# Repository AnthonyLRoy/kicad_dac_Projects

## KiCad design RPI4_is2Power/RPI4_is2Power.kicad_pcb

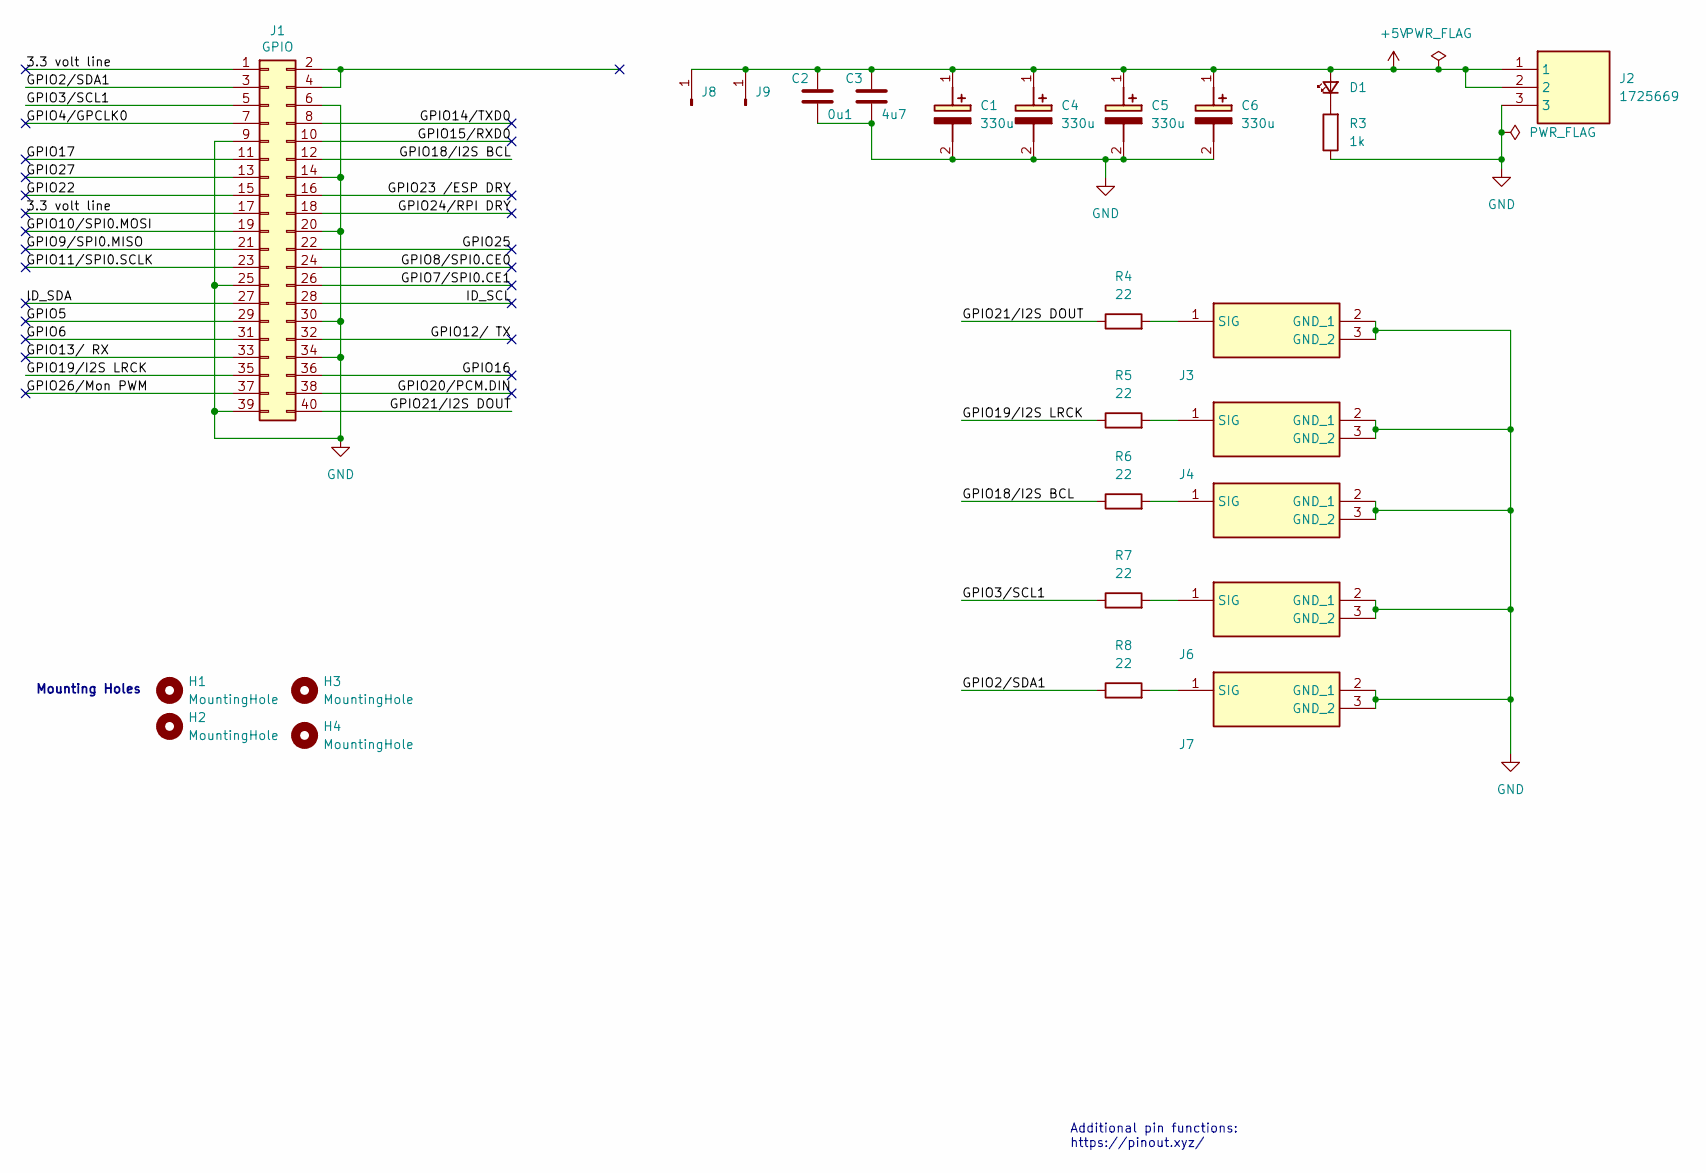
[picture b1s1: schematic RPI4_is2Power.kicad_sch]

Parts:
C1, C4, C5, C6: 330u; CAPPRD350W60D800H1300; Mouser Part Number 647-RNU1C331MDN1KX
C2: 0u1; C_0603_1608Metric_Pad1.08x0.95mm_HandSolder
C3: 4u7; CP_Radial_D5.0mm_P2.00mm
D1: LS_R976; LEDC2012X40N; Mouser Part Number 720-LSR976D5178
H1, H2, H3, H4: MountingHole; MountingHole_2.5mm
J1: GPIO; PinSocket_2x20_P2.54mm_Vertical
J2: 1725669; Mouser Part Number 651-1725669
J3, J4, J5, J6, J7: U.FL-R-SMT-1_80_; UFLRSMT180; Manufacturer_Part_Number U.FL-R-SMT-1(80)
J8, J9: Conn_01x01_Pin; Pin_D1.2mm_L11.3mm_W3.0mm_Flat
R3: 1k; R_0402_1005Metric
R4, R5, R6, R7, R8: 22; R_0402_1005Metric

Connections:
+5V: C1.1 (+), C2.1, C3.1, C4.1 (+), C5.1 (+), C6.1 (+), D1.2 (A), J2.1, J2.2, J8.1 (Pin_1_1), J9.1 (Pin_1_1)
/3.3 volt line: J1.1, J1.17
/GPIO2/SDA1: J1.3, R8.1
/GPIO3/SCL1: J1.5, R7.1
/GPIO4/GPCLK0: J1.7
/GPIO5: J1.29
/GPIO6: J1.31
/GPIO7/SPI0.CE1: J1.26
/GPIO8/SPI0.CE0: J1.24
/GPIO9/SPI0.MISO: J1.21
/GPIO10/SPI0.MOSI: J1.19
/GPIO11/SPI0.SCLK: J1.23
/GPIO12/ TX: J1.32
/GPIO13/ RX: J1.33
/GPIO14/TXD0: J1.8
/GPIO15/RXD0: J1.10
/GPIO16: J1.36
/GPIO17: J1.11
/GPIO18/I2S BCL: J1.12, R6.1
/GPIO19/I2S LRCK: J1.35, R5.1
/GPIO20/PCM.DIN: J1.38
/GPIO21/I2S DOUT: J1.40, R4.1
/GPIO22: J1.15
/GPIO23 /ESP DRY: J1.16
/GPIO24/RPI DRY: J1.18
/GPIO25: J1.22
/GPIO26/Mon PWM: J1.37
/GPIO27: J1.13
/ID_SCL: J1.28
/ID_SDA: J1.27
GND: C1.2 (-), C2.2, C3.2, C4.2 (-), C5.2 (-), C6.2 (-), J1.6, J1.9, J1.14, J1.20, J1.25, J1.30, J1.34, J1.39, J2.3, J3.2 (GND_1), J3.3 (GND_2), J4.2 (GND_1), J4.3 (GND_2), J5.2 (GND_1), J5.3 (GND_2), J6.2 (GND_1), J6.3 (GND_2), J7.2 (GND_1), J7.3 (GND_2), R3.1
unnamed: D1.1 (K), R3.2
unnamed: J3.1 (SIG), R4.2
unnamed: J4.1 (SIG), R5.2
unnamed: J5.1 (SIG), R6.2
unnamed: J6.1 (SIG), R7.2
unnamed: J7.1 (SIG), R8.2

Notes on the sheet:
Mounting Holes
Additional pin functions: https://pinout.xyz/

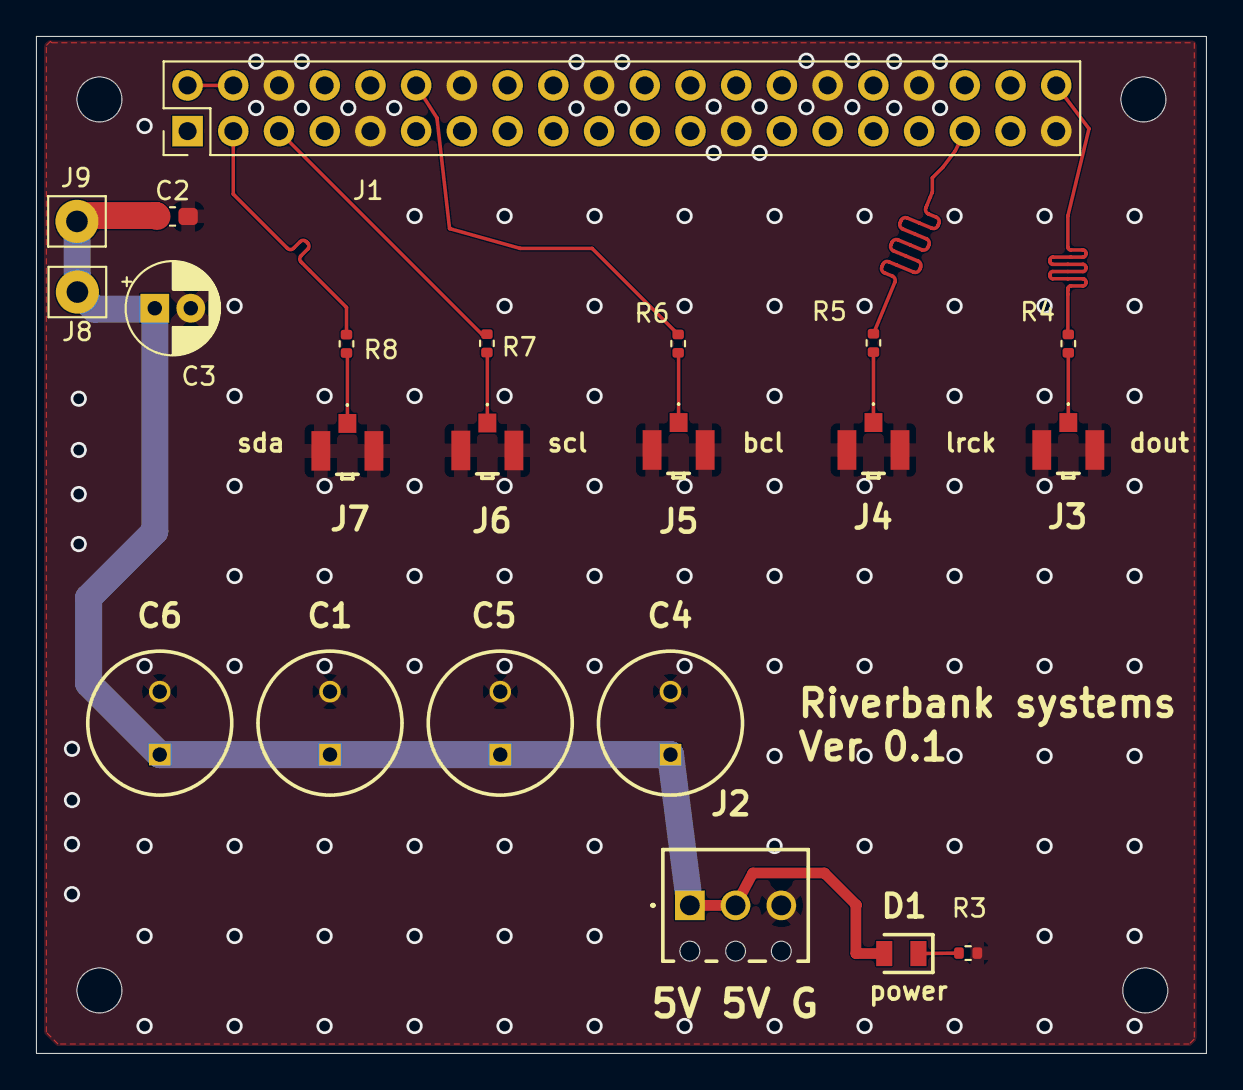
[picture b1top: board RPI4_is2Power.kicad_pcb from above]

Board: 2 copper layers, 65.0 x 56.5 mm, 26 parts (0 on the bottom side), 14 nets.

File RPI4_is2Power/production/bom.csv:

Designator,Footprint,Quantity,Value,LCSC Part #
"C1, C4, C5, C6",CAPPRD350W60D800H1300,4,330u,
C2,0603,1,0u1,
C3,CP_Radial_D5.0mm_P2.00mm,1,4u7,
D1,LEDC2012X40N,1,LS_R976,
"H1, H2, H3, H4",MountingHole_2.5mm,4,MountingHole,
J1,PinSocket_2x20_P2.54mm_Vertical,1,GPIO,
J2,1725669,1,1725669,
"J3, J4, J5, J6, J7",UFLRSMT180,5,U.FL-R-SMT-1_80_,
"J8, J9",Pin_D1.2mm_L11.3mm_W3.0mm_Flat,2,Conn_01x01_Pin,
R3,0402,1,1k,
"R4, R5, R6, R7, R8",0402,5,22,

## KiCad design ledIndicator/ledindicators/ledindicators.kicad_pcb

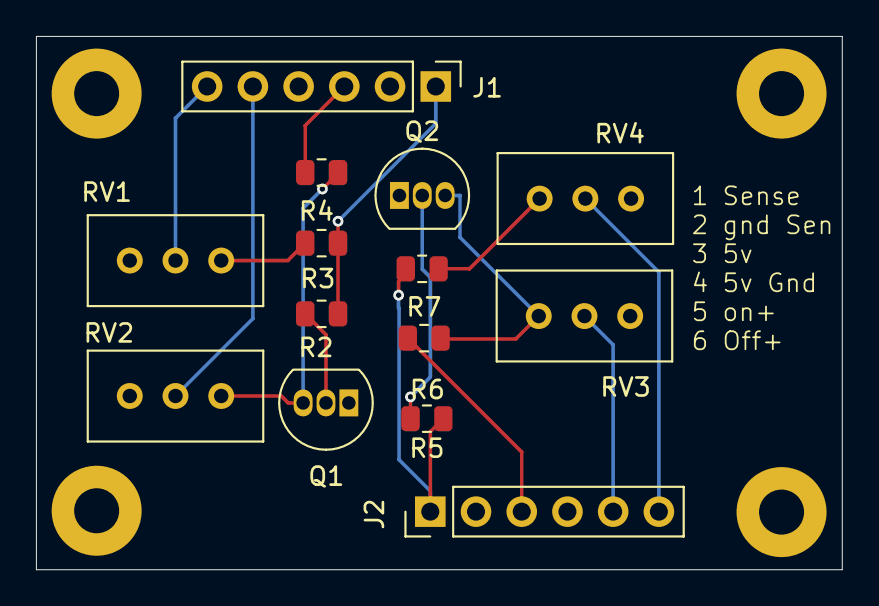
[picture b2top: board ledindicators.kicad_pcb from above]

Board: 2 copper layers, 44.8 x 29.6 mm, 18 parts (0 on the bottom side), 15 nets.

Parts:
H1, H2, H3, H4: MountingHole; MountingHole_2.5mm_Pad
J1, J2: Conn_01x06_Pin; PinHeader_1x06_P2.54mm_Vertical
Q1, Q2: 2N3904; TO-92_Inline
R2, R5: 10k; R_0805_2012Metric
R3, R4, R6, R7: 330R; R_0805_2012Metric
RV1, RV2, RV3, RV4: 100; Potentiometer_Bourns_3296W_Vertical

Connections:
GND: J1.2, J1.4, J2.2, J2.4, Q1.1 (E), Q2.1 (E)
unnamed: J1.1, R2.1, R3.2
unnamed: J1.3, R4.2
unnamed: J1.5, RV2.2
unnamed: J1.6, RV1.2
unnamed: J2.1, R5.1, R7.2
unnamed: J2.3, R6.2
unnamed: J2.5, RV3.2
unnamed: J2.6, RV4.2
unnamed: Q1.2 (B), R2.2
unnamed: Q1.3 (C), R4.1, RV2.1
unnamed: Q2.2 (B), R5.2
unnamed: Q2.3 (C), R6.1, RV3.1
unnamed: R3.1, RV1.1
unnamed: R7.1, RV4.1

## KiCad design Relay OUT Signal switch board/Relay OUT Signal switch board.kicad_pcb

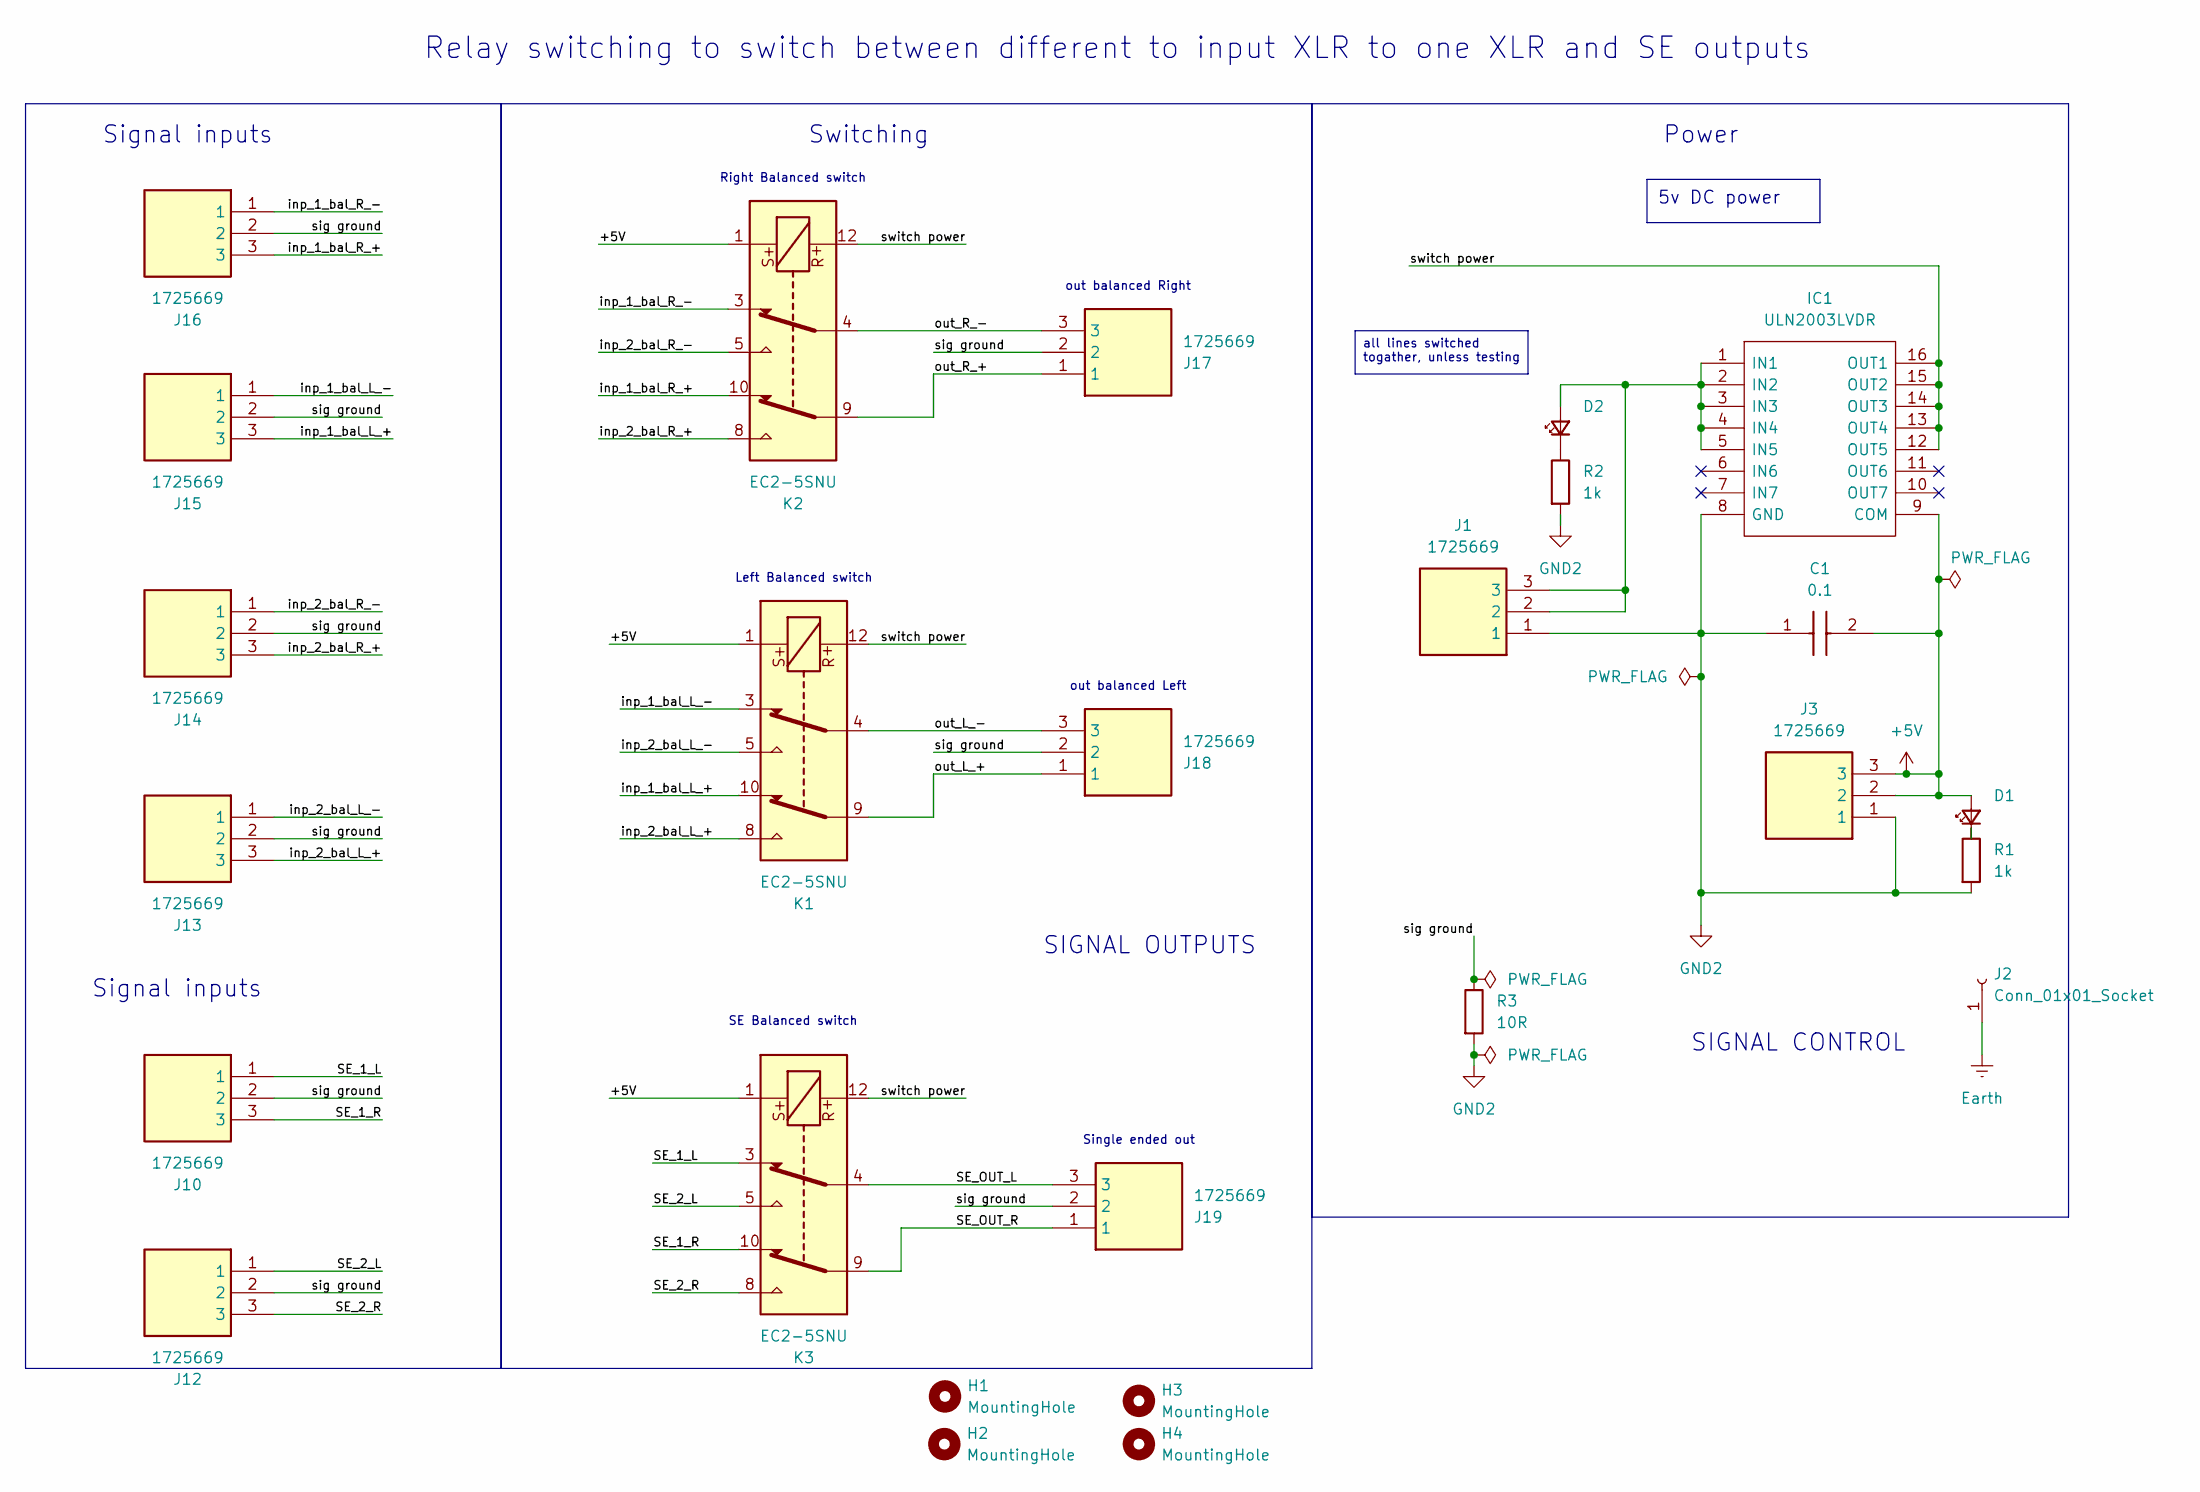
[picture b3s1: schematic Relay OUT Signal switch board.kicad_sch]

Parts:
C1: 0.1; C_0603_1608Metric; Mouser Part Number 80-C0603C104K4R3190
D1, D2: LS_R976; LEDC2012X40N; Mouser Part Number 720-LSR976D5178
H1, H2, H3, H4: MountingHole; MountingHole_2.5mm
IC1: ULN2003LVDR; SOIC127P780X200-16N; Manufacturer_Part_Number ULN2003LVDR; Mouser Part Number 595-ULN2003LVDR
J1, J3, J10, J12, J13, J14, J15, J16, J17, J18, J19: 1725669; Mouser Part Number 651-1725669
J2: Conn_01x01_Socket; PinHeader_1x01_P1.00mm_Vertical
K1, K2, K3: EC2-5SNU; Relay_DPDT_Kemet_EC2
R1, R2: 1k; R_0603_1608Metric
R3: 10R; R_0603_1608Metric

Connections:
+5V: C1.2, D1.2 (A), IC1.9 (COM), J3.2, J3.3, K1.1, K2.1, K3.1
/SE_1_L: J10.1, K3.3
/SE_1_R: J10.3, K3.10
/SE_2_L: J12.1, K3.5
/SE_2_R: J12.3, K3.8
/SE_OUT_L: J19.3, K3.4
/SE_OUT_R: J19.1, K3.9
/inp_1_bal_L_+: J15.3, K1.10
/inp_1_bal_L_-: J15.1, K1.3
/inp_1_bal_R_+: J16.3, K2.10
/inp_1_bal_R_-: J16.1, K2.3
/inp_2_bal_L_+: J13.3, K1.8
/inp_2_bal_L_-: J13.1, K1.5
/inp_2_bal_R_+: J14.3, K2.8
/inp_2_bal_R_-: J14.1, K2.5
/out_L_+: J18.1, K1.9
/out_L_-: J18.3, K1.4
/out_R_+: J17.1, K2.9
/out_R_-: J17.3, K2.4
/sig ground: J10.2, J12.2, J13.2, J14.2, J15.2, J16.2, J17.2, J18.2, J19.2, R3.1
Earth: J2.1
GND2: C1.1, IC1.8 (GND), J1.1, J3.1, R1.2, R2.2, R3.2
unnamed: D1.1 (K), R1.1
unnamed: D2.1 (K), R2.1

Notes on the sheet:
all lines switched togather, unless testing
5v DC power
out balanced Left
Left Balanced switch
Switching
Power
out balanced Right
Single ended out
Signal inputs
SIGNAL CONTROL
SE Balanced switch
Relay switching to switch between different to input XLR to one XLR and SE outputs
Right Balanced switch
SIGNAL OUTPUTS

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
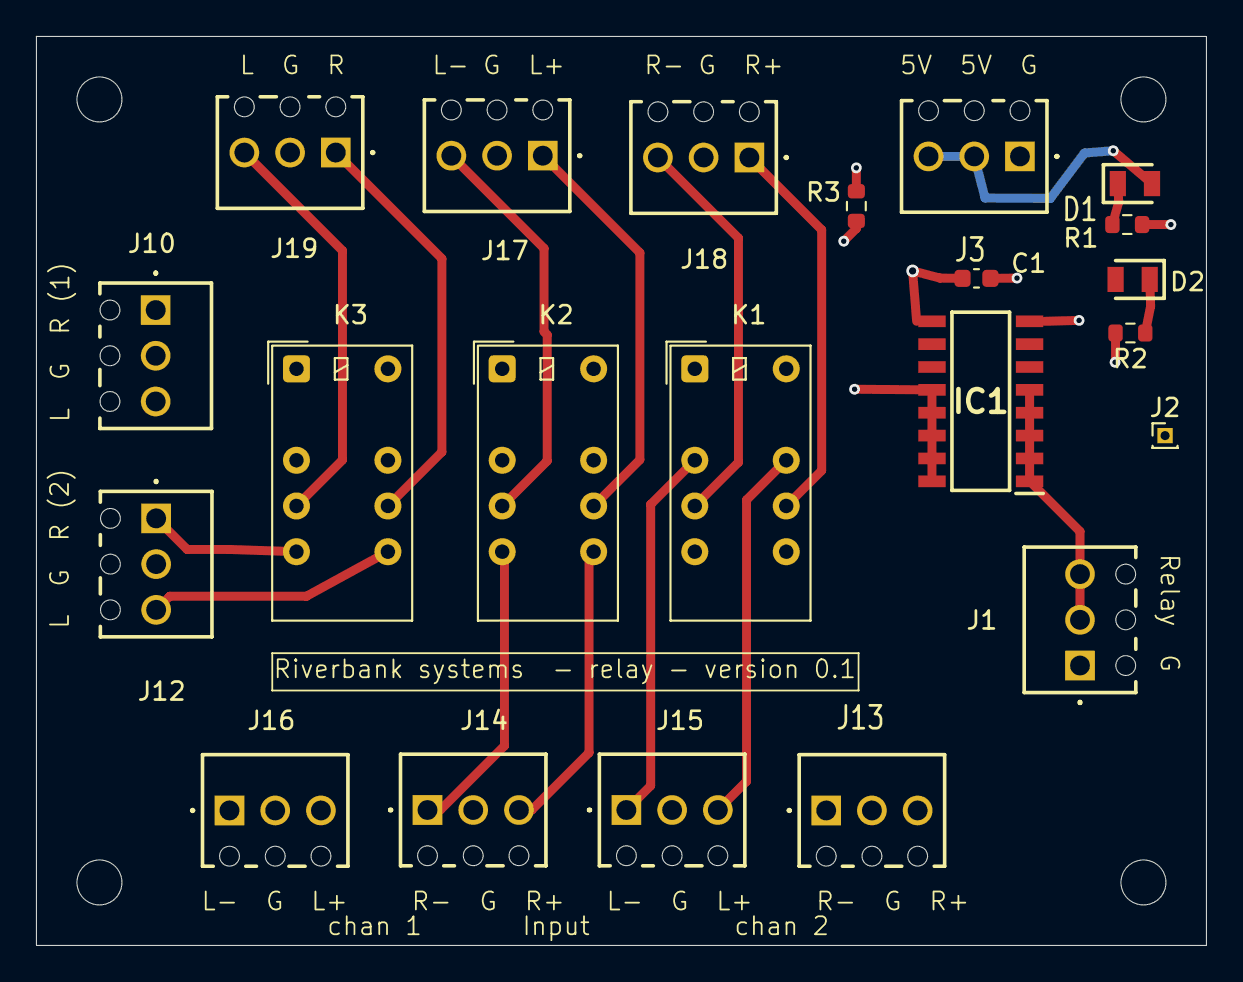
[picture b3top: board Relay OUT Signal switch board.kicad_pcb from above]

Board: 6 copper layers, 65.0 x 50.5 mm, 26 parts (0 on the bottom side), 25 nets.

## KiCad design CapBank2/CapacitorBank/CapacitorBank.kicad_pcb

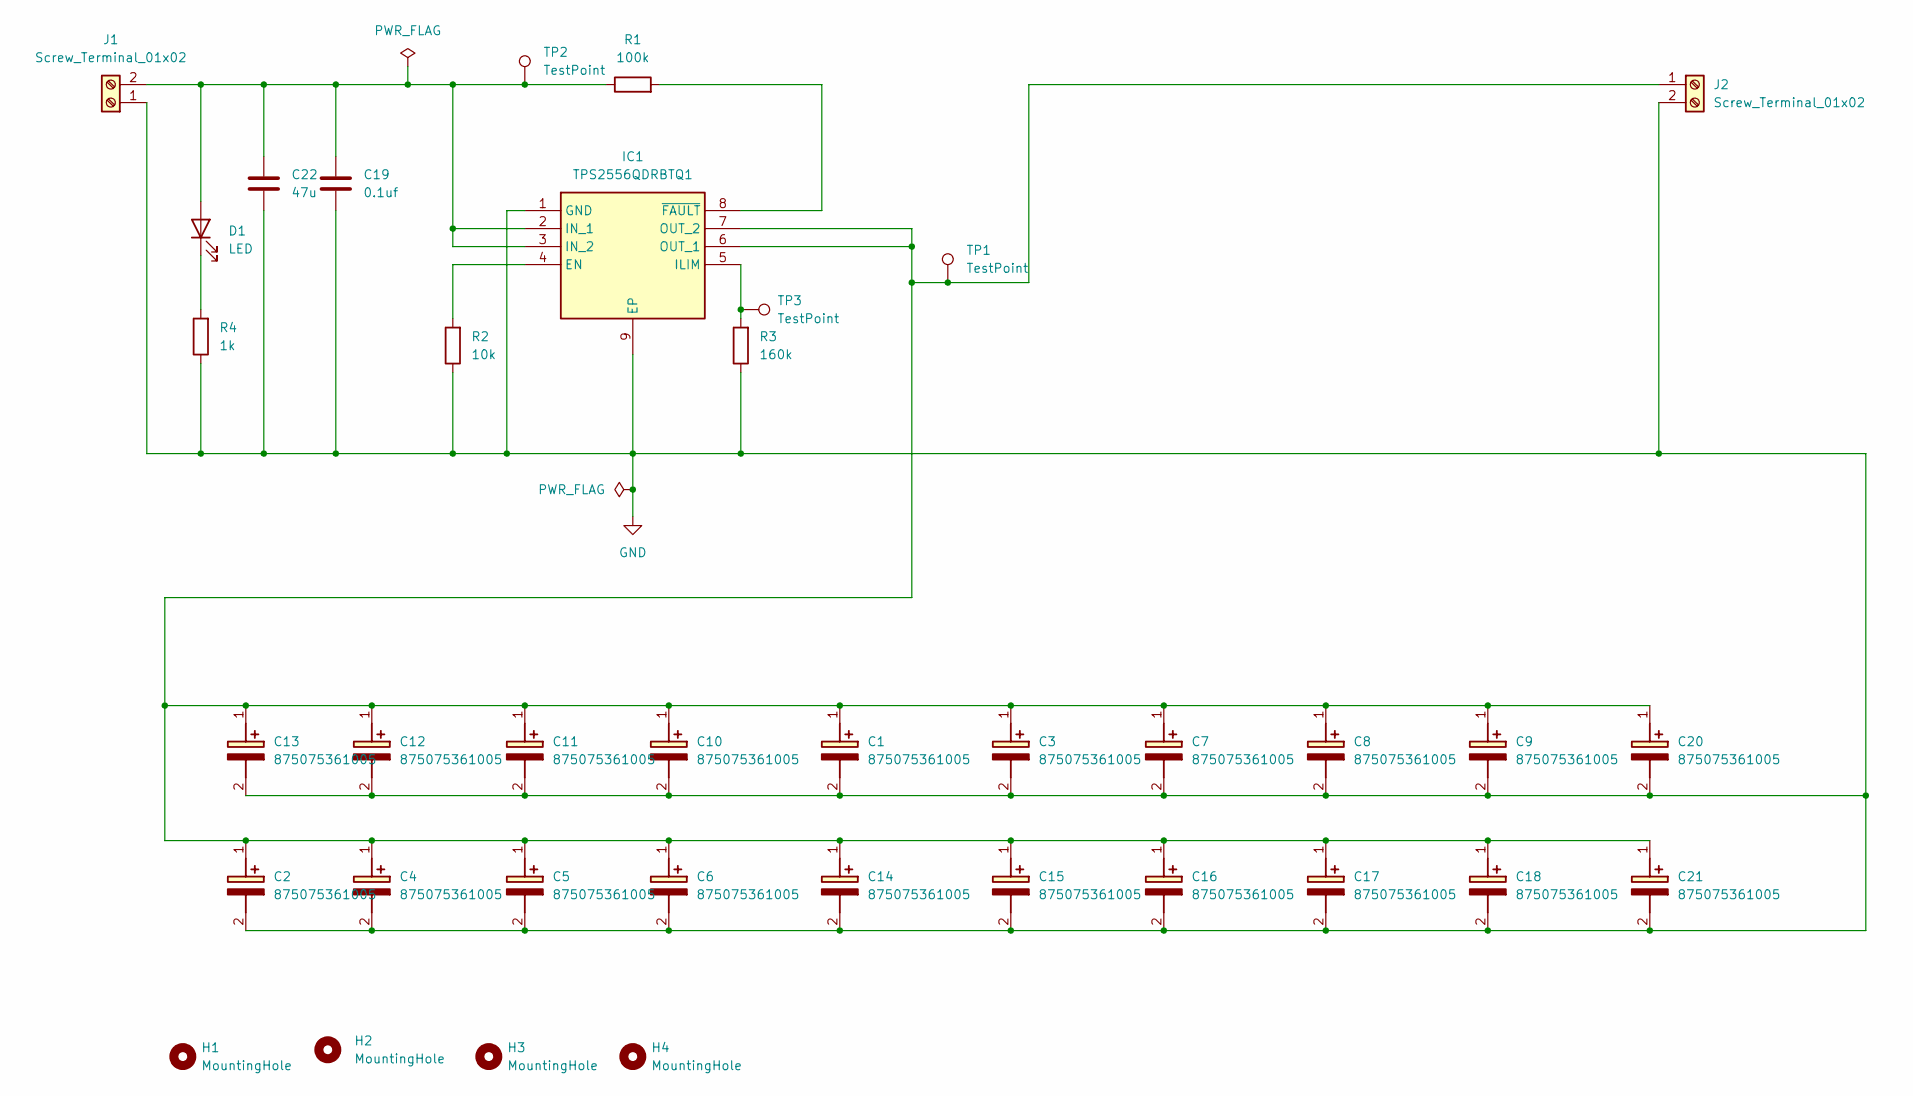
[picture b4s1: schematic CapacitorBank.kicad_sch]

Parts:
C1, C2, C3, C4, C5, C6, C7, C8, C9, C10, C11, C12, C13, C14, C15, C16, C17, C18, C20, C21: 875075361005; CAPAE1030X1270N; Mouser Part Number 710-875075361005
C19: 0.1uf; C_0805_2012Metric
C22: 47u; C_0805_2012Metric
D1: LED; LED_0603_1608Metric_Pad1.05x0.95mm_HandSolder
H1, H2, H3, H4: MountingHole; MountingHole_3.2mm_M3
IC1: TPS2556QDRBTQ1; SON65P300X300X100-9N-D; Mouser Part Number 595-TPS2556QDRBTQ1
J1, J2: Screw_Terminal_01x02; TerminalBlock_483132_2P_P7.62mm
R1: 100k; R_0805_2012Metric_Pad1.20x1.40mm_HandSolder
R2: 10k; R_0805_2012Metric_Pad1.20x1.40mm_HandSolder
R3: 160k; R_0805_2012Metric_Pad1.20x1.40mm_HandSolder
R4: 1k; R_0805_2012Metric_Pad1.20x1.40mm_HandSolder
TP1, TP2, TP3: TestPoint; TestPoint_Pad_1.5x1.5mm

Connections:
GND: C1.2 (-), C2.2 (-), C3.2 (-), C4.2 (-), C5.2 (-), C6.2 (-), C7.2 (-), C8.2 (-), C9.2 (-), C10.2 (-), C11.2 (-), C12.2 (-), C13.2 (-), C14.2 (-), C15.2 (-), C16.2 (-), C17.2 (-), C18.2 (-), C19.2, C20.2 (-), C21.2 (-), C22.2, IC1.1 (GND), IC1.9 (EP), J1.1, J2.2, R2.1, R3.1, R4.1
unnamed: C1.1 (+), C2.1 (+), C3.1 (+), C4.1 (+), C5.1 (+), C6.1 (+), C7.1 (+), C8.1 (+), C9.1 (+), C10.1 (+), C11.1 (+), C12.1 (+), C13.1 (+), C14.1 (+), C15.1 (+), C16.1 (+), C17.1 (+), C18.1 (+), C20.1 (+), C21.1 (+), IC1.6 (OUT_1), IC1.7 (OUT_2), J2.1, TP1.1
unnamed: C19.1, C22.1, D1.2 (A), IC1.2 (IN_1), IC1.3 (IN_2), J1.2, R1.1, TP2.1
unnamed: D1.1 (K), R4.2
unnamed: IC1.4 (EN), R2.2
unnamed: IC1.5 (ILIM), R3.2, TP3.1
unnamed: IC1.8 (~FAULT), R1.2

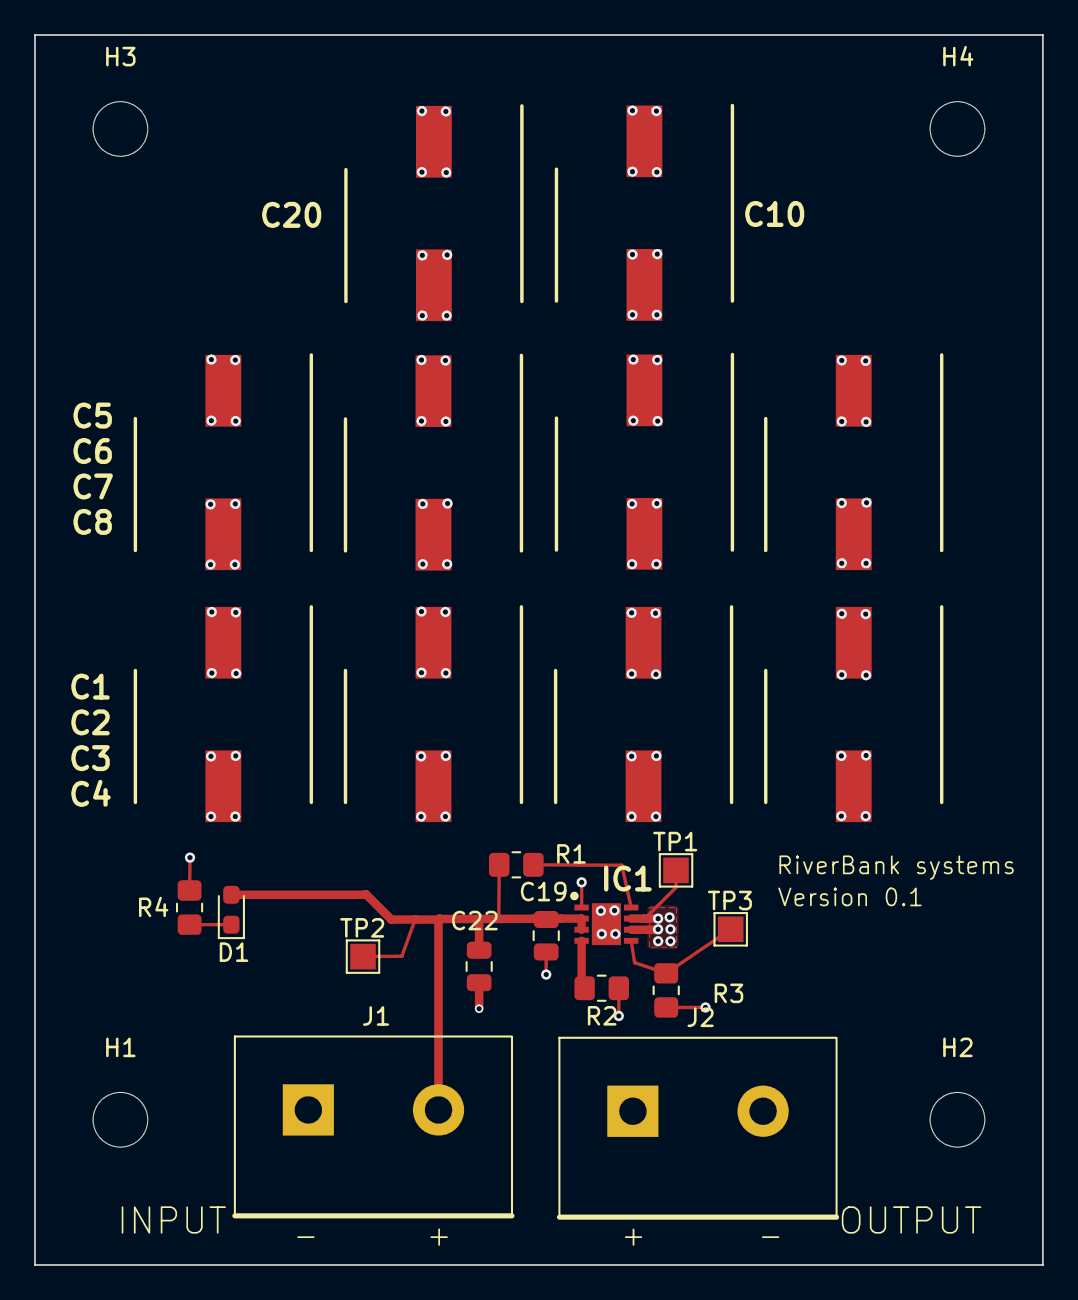
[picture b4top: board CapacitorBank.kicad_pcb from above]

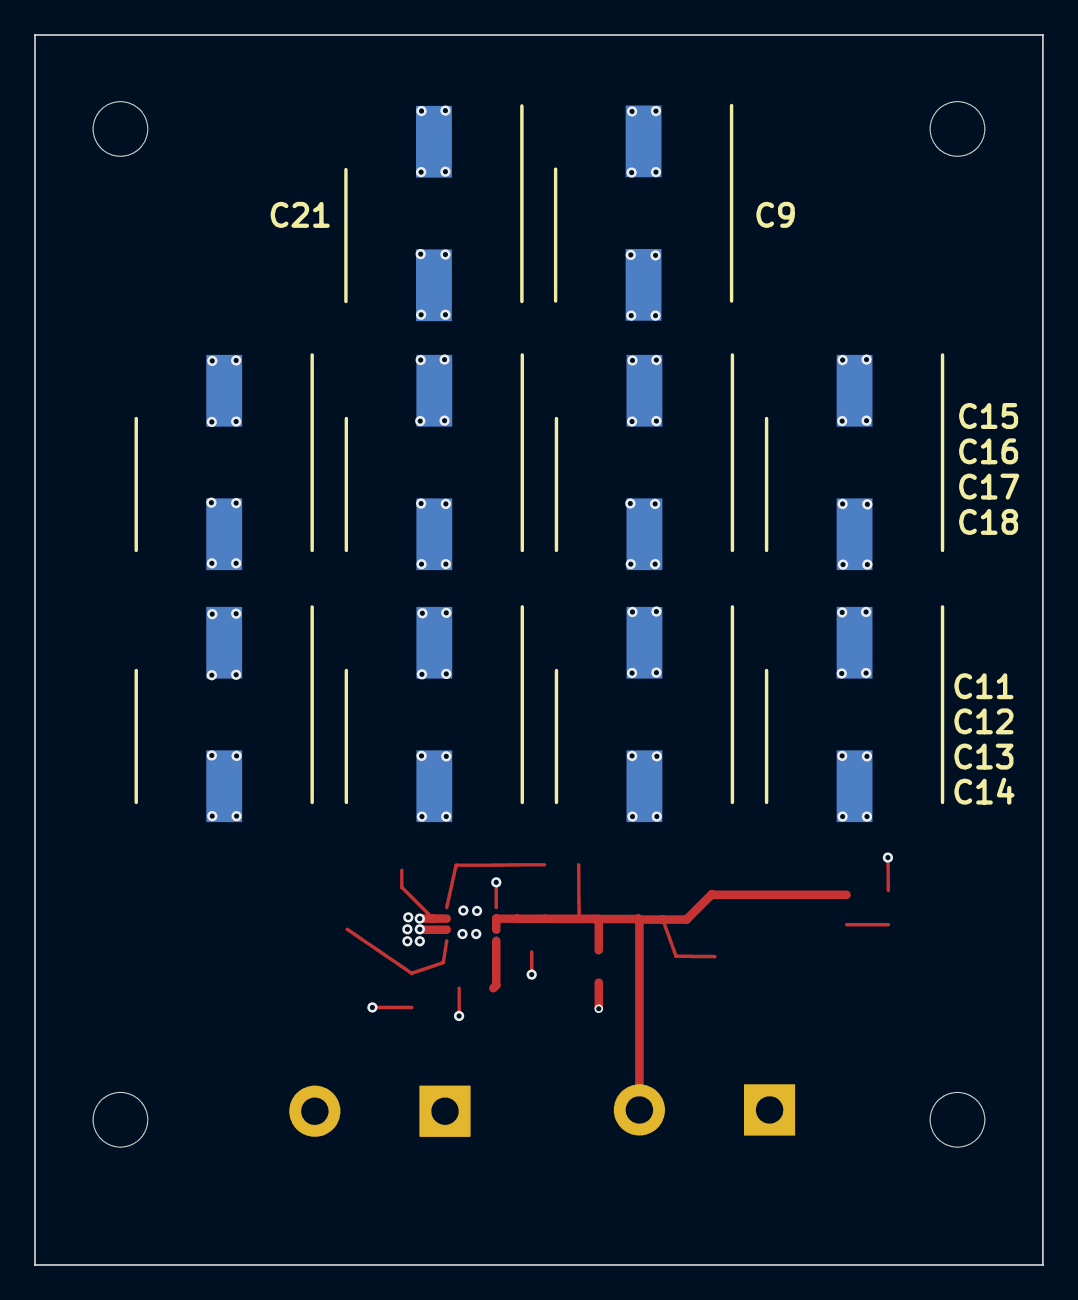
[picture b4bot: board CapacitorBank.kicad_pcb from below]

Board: 4 copper layers, 59.0 x 72.0 mm, 37 parts (10 on the bottom side), 7 nets.

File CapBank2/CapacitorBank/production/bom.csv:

Designator,Footprint,Quantity,Value,LCSC Part #
"C1, C10, C11, C12, C13, C14, C15, C16, C17, C18, C2, C20, C21, C3, C4, C5, C6, C7, C8, C9",CAPAE1030X1270N,20,875075361005,
C19,0805,1,0.1uf,
C22,0805,1,47u,
D1,0603,1,LED,
"H1, H2, H3, H4",MountingHole_3.2mm_M3,4,MountingHole,
IC1,SON65P300X300X100-9N-D,1,TPS2556QDRBTQ1,
"J1, J2",TerminalBlock_483132_2P_P7.62mm,2,Screw_Terminal_01x02,
R1,0805,1,100k,
R2,0805,1,10k,
R3,0805,1,160k,
R4,0805,1,1k,
"TP1, TP2, TP3",TestPoint_Pad_1.5x1.5mm,3,TestPoint,
